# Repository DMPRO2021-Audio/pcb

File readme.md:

# PCB for synth project thingy

## [Bill of materials (google sheets)](https://docs.google.com/spreadsheets/d/1mw8S-eOHjplATXsi4Le0auCMZ8W1ZmBKjRO5l_0JOso/edit#gid=0)

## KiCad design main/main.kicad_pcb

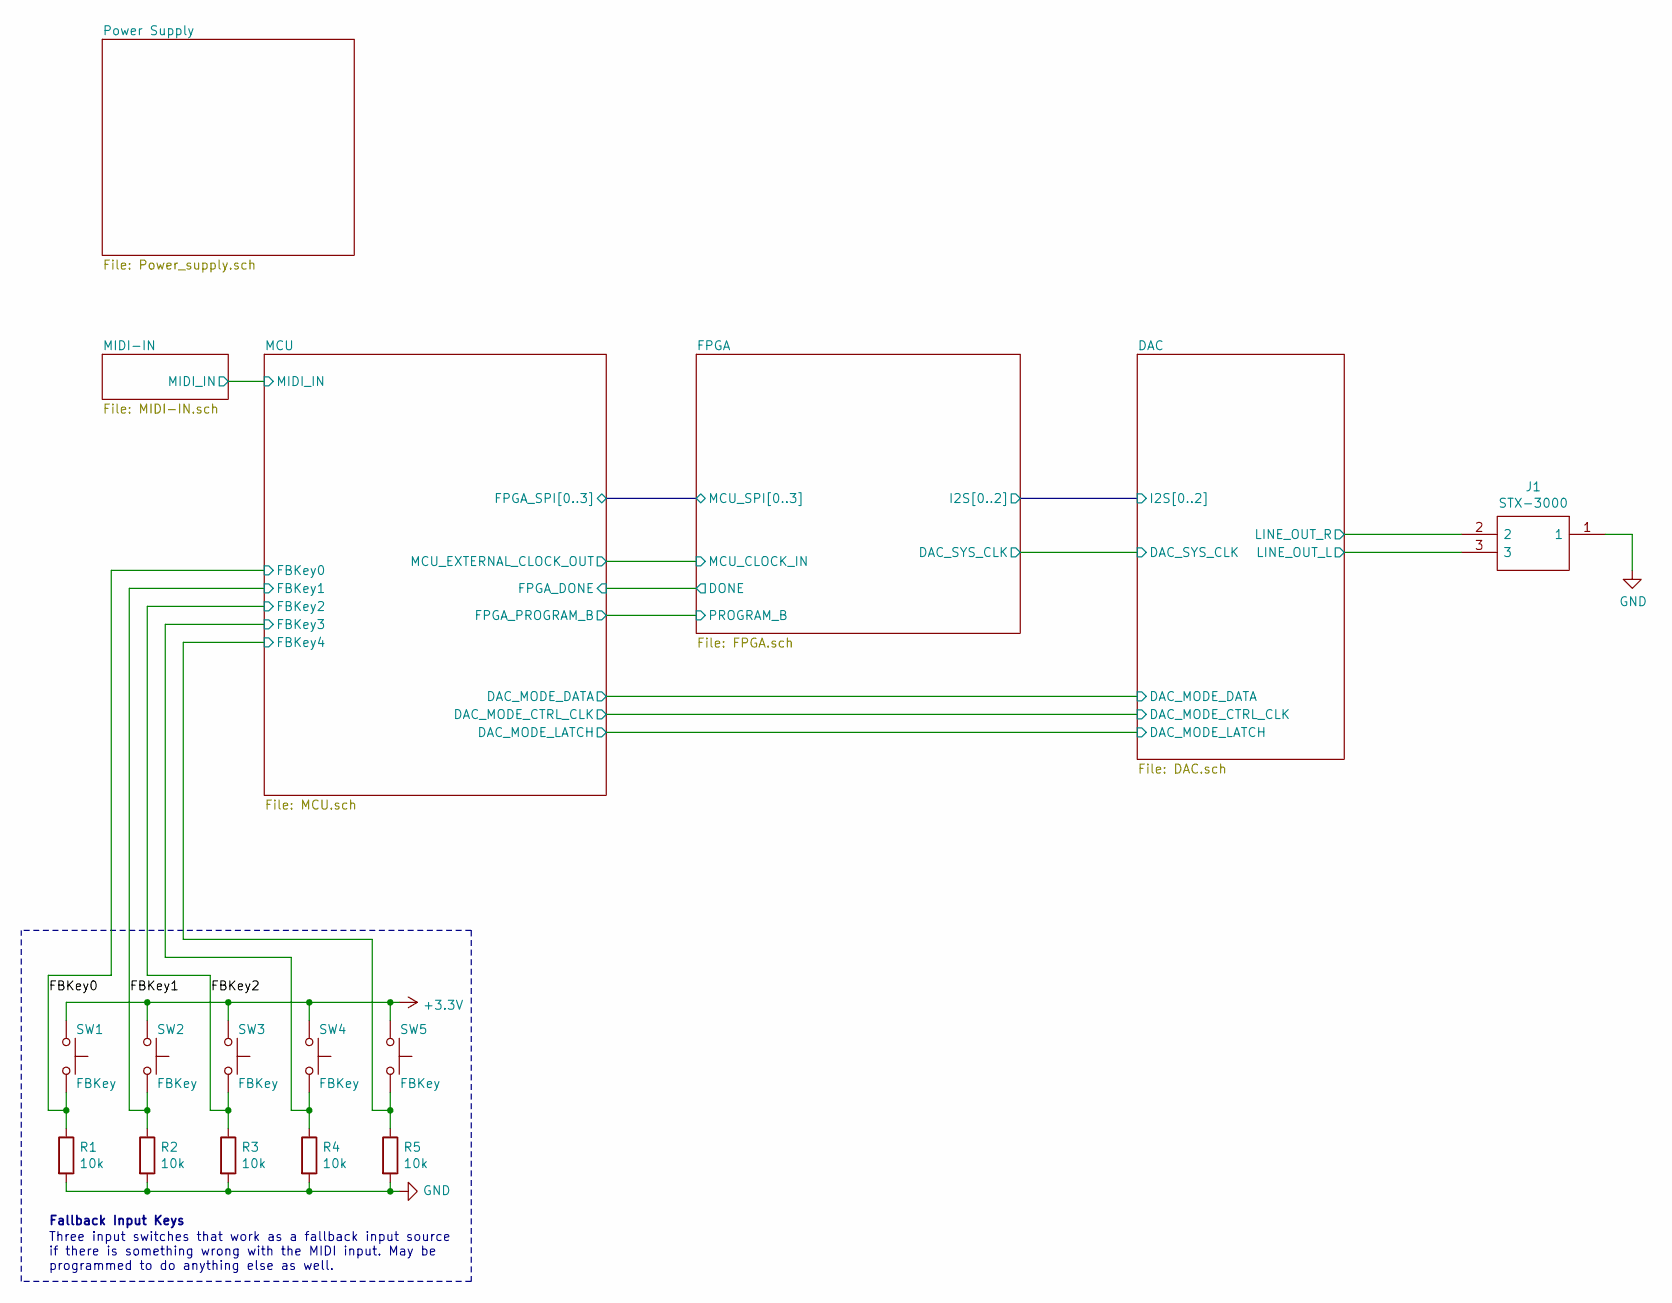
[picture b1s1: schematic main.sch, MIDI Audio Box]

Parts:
J1: STX-3000; STX3000; Manufacturer_Part_Number STX-3000
R1, R2, R3, R4, R5: 10k; R_0805_2012Metric_Pad1.20x1.40mm_HandSolder
SW1, SW2, SW3, SW4, SW5: FBKey; SW_Push_1P1T_NO_6x6mm_H9.5mm; Manufacturer_Part_Number PTS645SM43SMTR92 LFS

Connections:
+3V3: SW1.1, SW2.1, SW3.1, SW4.1, SW5.1; also elsewhere on the board
/DAC/LINE_OUT_L: J1.3; also elsewhere on the board
/DAC/LINE_OUT_R: J1.2; also elsewhere on the board
/FBKey0: R1.1, SW1.2; also elsewhere on the board
/FBKey1: R2.1, SW2.2; also elsewhere on the board
/FBKey2: R3.1, SW3.2; also elsewhere on the board
/MCU/FBKey3: R4.1, SW4.2; also elsewhere on the board
/MCU/FBKey4: R5.1, SW5.2; also elsewhere on the board
GND: J1.1, R1.2, R2.2, R3.2, R4.2, R5.2; also elsewhere on the board

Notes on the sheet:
Fallback Input Keys
Three input switches that work as a fallback input source if there is something wrong with the MIDI input. May be programmed to do anything else as well.

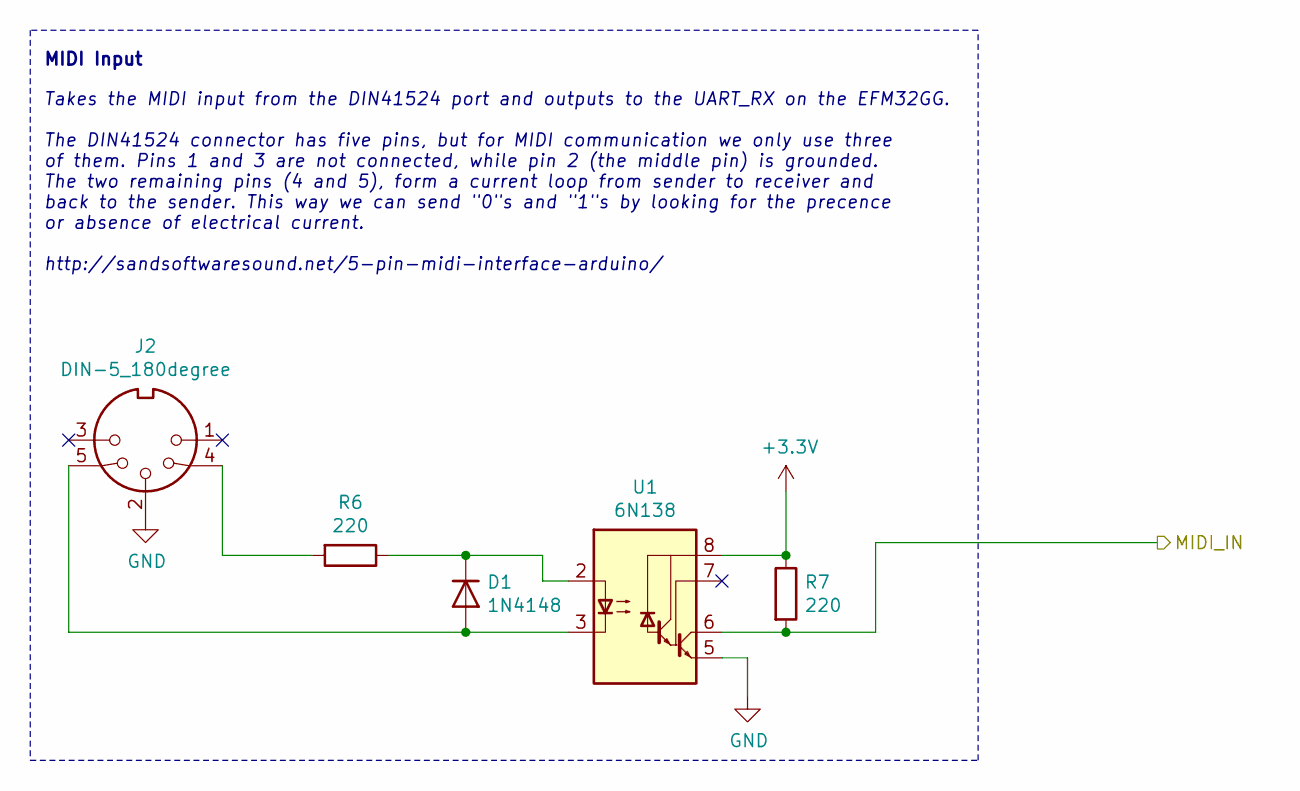
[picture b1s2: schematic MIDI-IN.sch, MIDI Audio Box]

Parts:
D1: 1N4148; D_SOD-123F; Manufacturer_Part_Number 1N4148W RH
J2: DIN-5_180degree; 671-0501; Manufacturer_Part_Number 671-0501
R6, R7: 220; R_0805_2012Metric_Pad1.20x1.40mm_HandSolder
U1: 6N138; SOP254P1030X460-8N; Manufacturer_Part_Number 6N138SMT/R

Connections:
+3V3: R7.1, U1.8 (VCC); also elsewhere on the board
/MCU/MIDI_IN: R7.2, U1.6 (VO2); also elsewhere on the board
GND: J2.2, U1.5 (GND); also elsewhere on the board
unnamed: D1.1 (K), R6.1, U1.2 (C1)
unnamed: D1.2 (A), J2.5, U1.3 (C2)
unnamed: J2.4, R6.2

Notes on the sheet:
MIDI Input
Takes the MIDI input from the DIN41524 port and outputs to the UART_RX on the EFM32GG. The DIN41524 connector has five pins, but for MIDI communication we only use three of them. Pins 1 and 3 are not connected, while pin 2 (the middle pin) is grounded. The two remaining pins (4 and 5), form a curre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

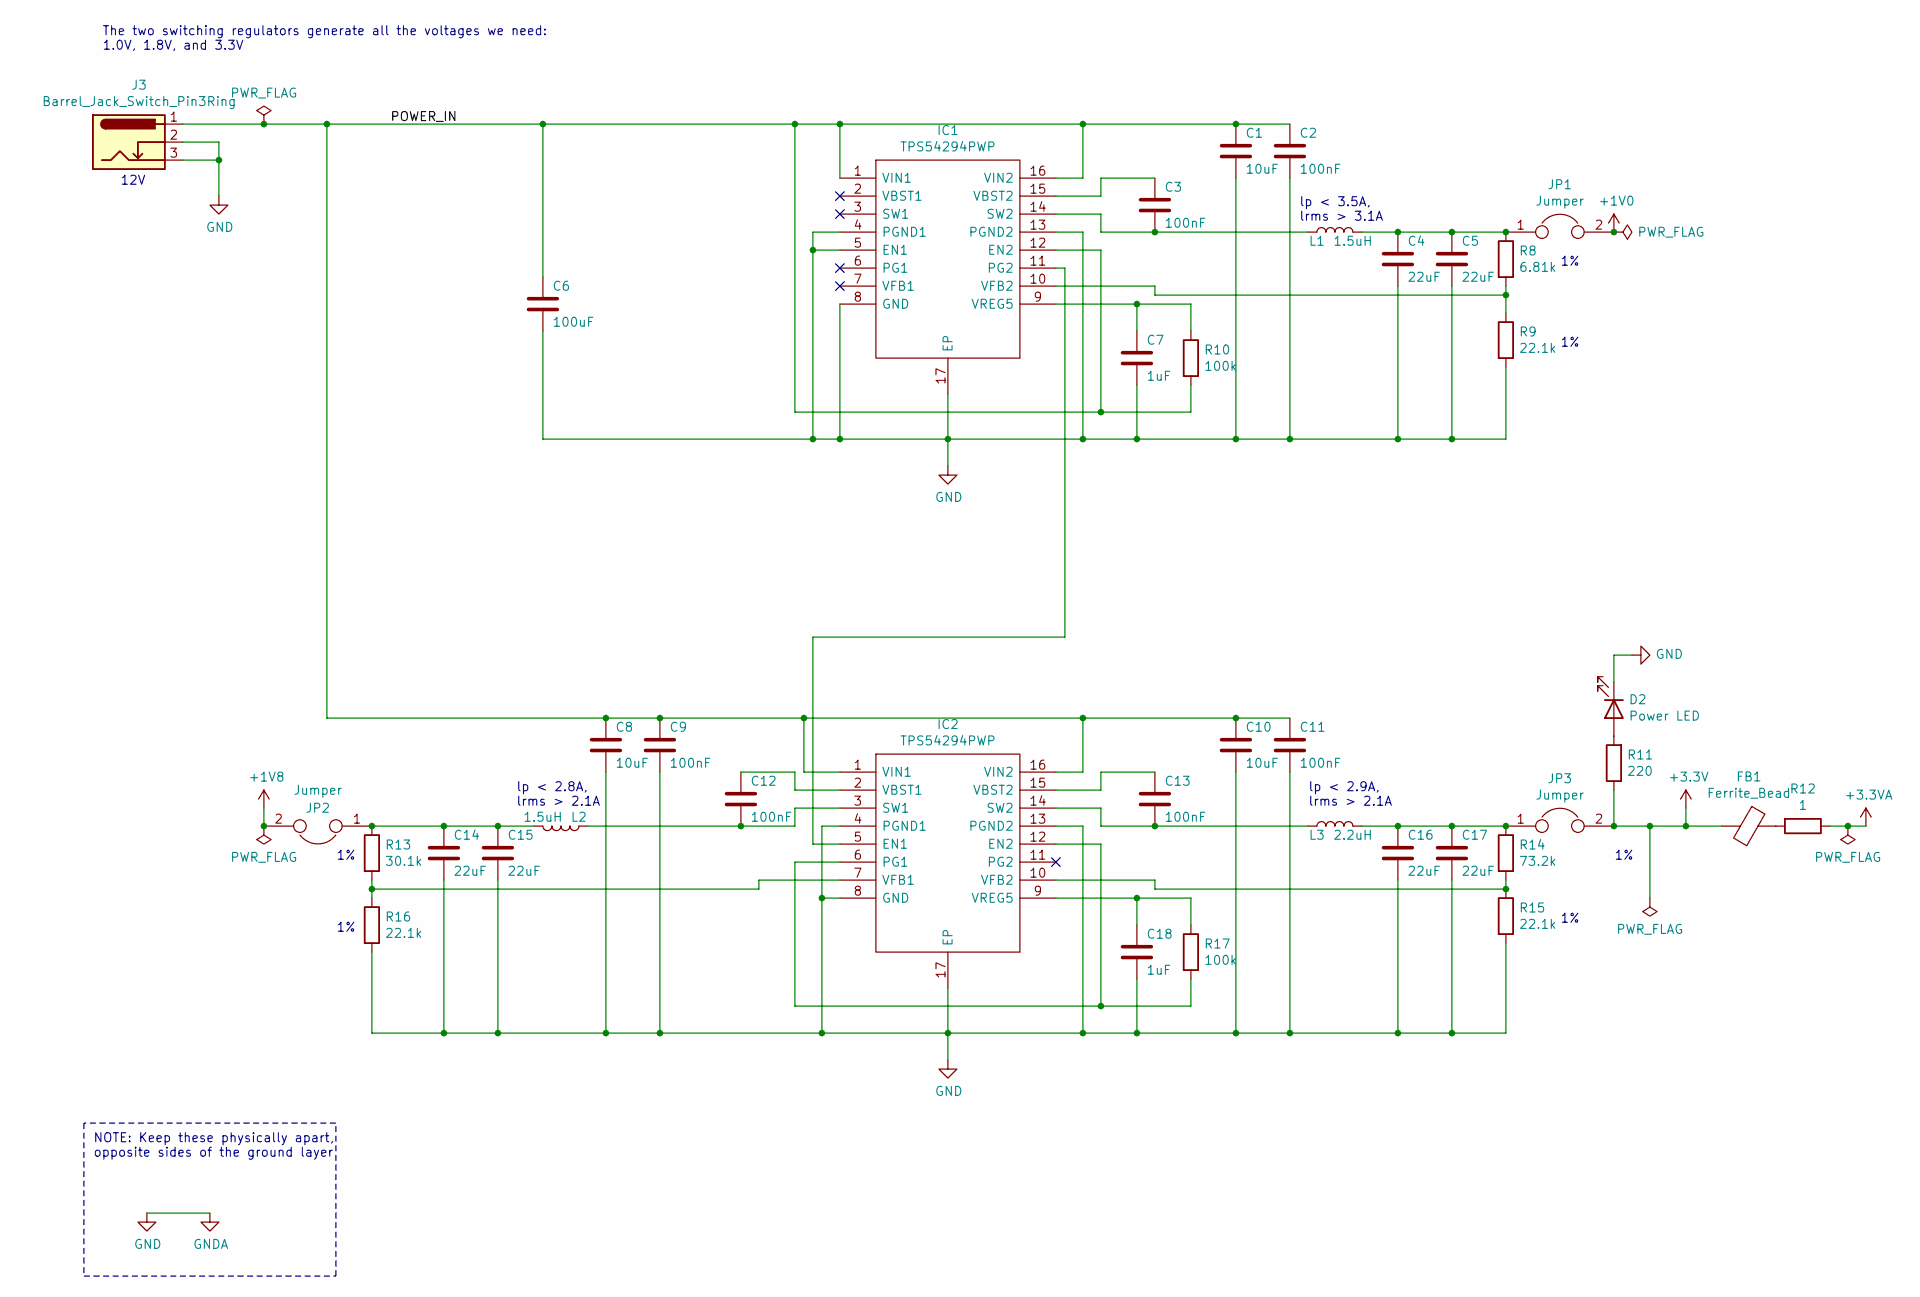
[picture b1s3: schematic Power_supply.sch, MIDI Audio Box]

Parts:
C1, C8, C10: 10uF; C_0805_2012Metric_Pad1.18x1.45mm_HandSolder
C2, C3, C9, C11, C12, C13: 100nF; C_0805_2012Metric_Pad1.18x1.45mm_HandSolder
C4, C5, C14, C15, C16, C17: 22uF; C_0805_2012Metric_Pad1.18x1.45mm_HandSolder
C6: 100uF; C_1210_3225Metric_Pad1.33x2.70mm_HandSolder
C7, C18: 1uF; C_0805_2012Metric_Pad1.18x1.45mm_HandSolder
D2: Power LED; LED_0805_2012Metric_Pad1.15x1.40mm_HandSolder; Manufacturer_Part_Number 150080RS75000
FB1: Ferrite_Bead; R_0805_2012Metric_Pad1.20x1.40mm_HandSolder; Manufacturer_Part_Number BMB2A0060LN2
IC1, IC2: TPS54294PWP; Manufacturer_Part_Number TPS54294PWP; Mouser Part Number 595-TPS54294PWP
J3: Barrel_Jack_Switch_Pin3Ring; BarrelJack_CUI_PJ-102AH_Horizontal; Manufacturer_Part_Number PJ-002A
JP1, JP2, JP3: Jumper; PinHeader_2x01_P2.54mm_Vertical
L1, L2: 1.5uH; L_1806_4516Metric_Pad1.57x1.80mm_HandSolder; Manufacturer_Part_Number 1286AS-H-2R2M=P2
L3: 2.2uH; L_1806_4516Metric_Pad1.57x1.80mm_HandSolder; Manufacturer_Part_Number DFE201610E-1R5M=P2
R8: 6.81k; R_0805_2012Metric_Pad1.20x1.40mm_HandSolder
R9, R15, R16: 22.1k; R_0805_2012Metric_Pad1.20x1.40mm_HandSolder
R10, R17: 100k; R_0805_2012Metric_Pad1.20x1.40mm_HandSolder
R11: 220; R_0805_2012Metric_Pad1.20x1.40mm_HandSolder
R12: 1; R_0805_2012Metric_Pad1.20x1.40mm_HandSolder
R13: 30.1k; R_0805_2012Metric_Pad1.20x1.40mm_HandSolder
R14: 73.2k; R_0805_2012Metric_Pad1.20x1.40mm_HandSolder

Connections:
+1V0: JP1.2; also elsewhere on the board
+1V8: JP2.2; also elsewhere on the board
+3.3VA: R12.1; also elsewhere on the board
+3V3: FB1.2, JP3.2, R11.1; also elsewhere on the board
/Power Supply/POWER_IN: C1.1, C2.1, C6.1, C8.1, C9.1, C10.1, C11.1, IC1.1 (VIN1), IC1.12 (EN2), IC1.16 (VIN2), IC2.1 (VIN1), IC2.16 (VIN2), J3.1, R10.2
GND: C1.2, C2.2, C4.2, C5.2, C6.2, C7.2, C8.2, C9.2, C10.2, C11.2, C14.2, C15.2, C16.2, C17.2, C18.2, D2.1 (K), IC1.4 (PGND1), IC1.5 (EN1), IC1.8 (GND), IC1.13 (PGND2), IC1.17 (EP), IC2.4 (PGND1), IC2.8 (GND), IC2.13 (PGND2), IC2.17 (EP), J3.2, J3.3, R9.2, R15.2, R16.2; also elsewhere on the board
unnamed: C3.1, IC1.15 (VBST2)
unnamed: C3.2, IC1.14 (SW2), L1.1
unnamed: C4.1, C5.1, JP1.1, L1.2, R8.1
unnamed: C7.1, IC1.9 (VREG5), R10.1
unnamed: C12.1, IC2.2 (VBST1)
unnamed: C12.2, IC2.3 (SW1), L2.1
unnamed: C13.1, IC2.15 (VBST2)
unnamed: C13.2, IC2.14 (SW2), L3.1
unnamed: C14.1, C15.1, JP2.1, L2.2, R13.1
unnamed: C16.1, C17.1, JP3.1, L3.2, R14.1
unnamed: C18.1, IC2.9 (VREG5), R17.1
unnamed: D2.2 (A), R11.2
unnamed: FB1.1, R12.2
unnamed: IC1.10 (VFB2), R8.2, R9.1
unnamed: IC1.11 (PG2), IC2.5 (EN1)
unnamed: IC2.7 (VFB1), R13.2, R16.1
unnamed: IC2.10 (VFB2), R14.2, R15.1
unnamed: IC2.6 (PG1), IC2.12 (EN2), R17.2

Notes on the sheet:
lp < 2.8A, lrms > 2.1A
lp < 2.9A, lrms > 2.1A
12V
lp < 3.5A, lrms > 3.1A
The two switching regulators generate all the voltages we need: 1.0V, 1.8V, and 3.3V
NOTE: Keep these physically apart, opposite sides of the ground layer

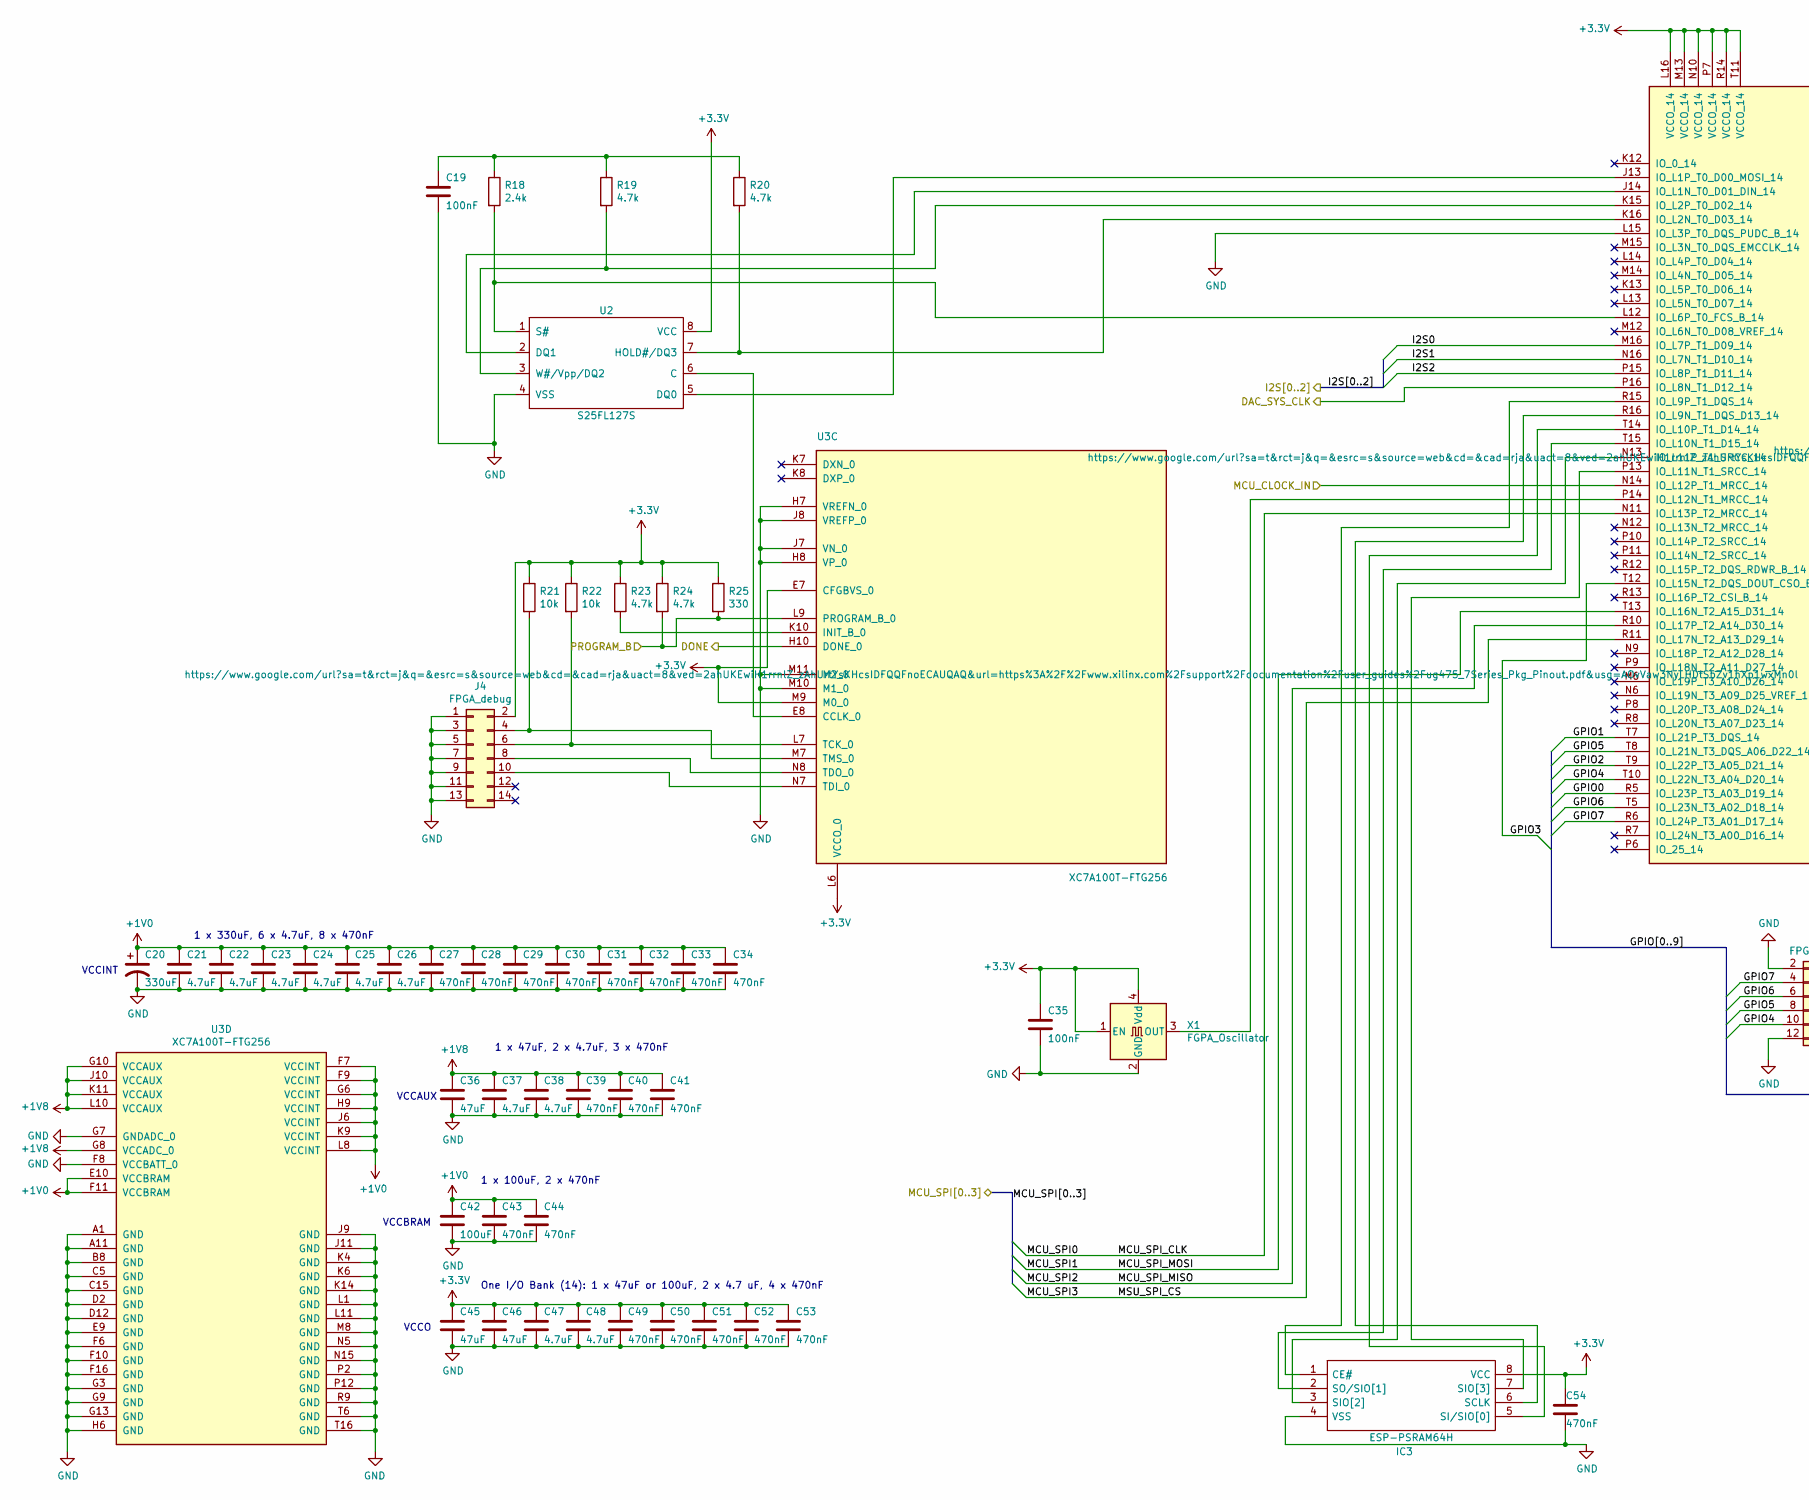
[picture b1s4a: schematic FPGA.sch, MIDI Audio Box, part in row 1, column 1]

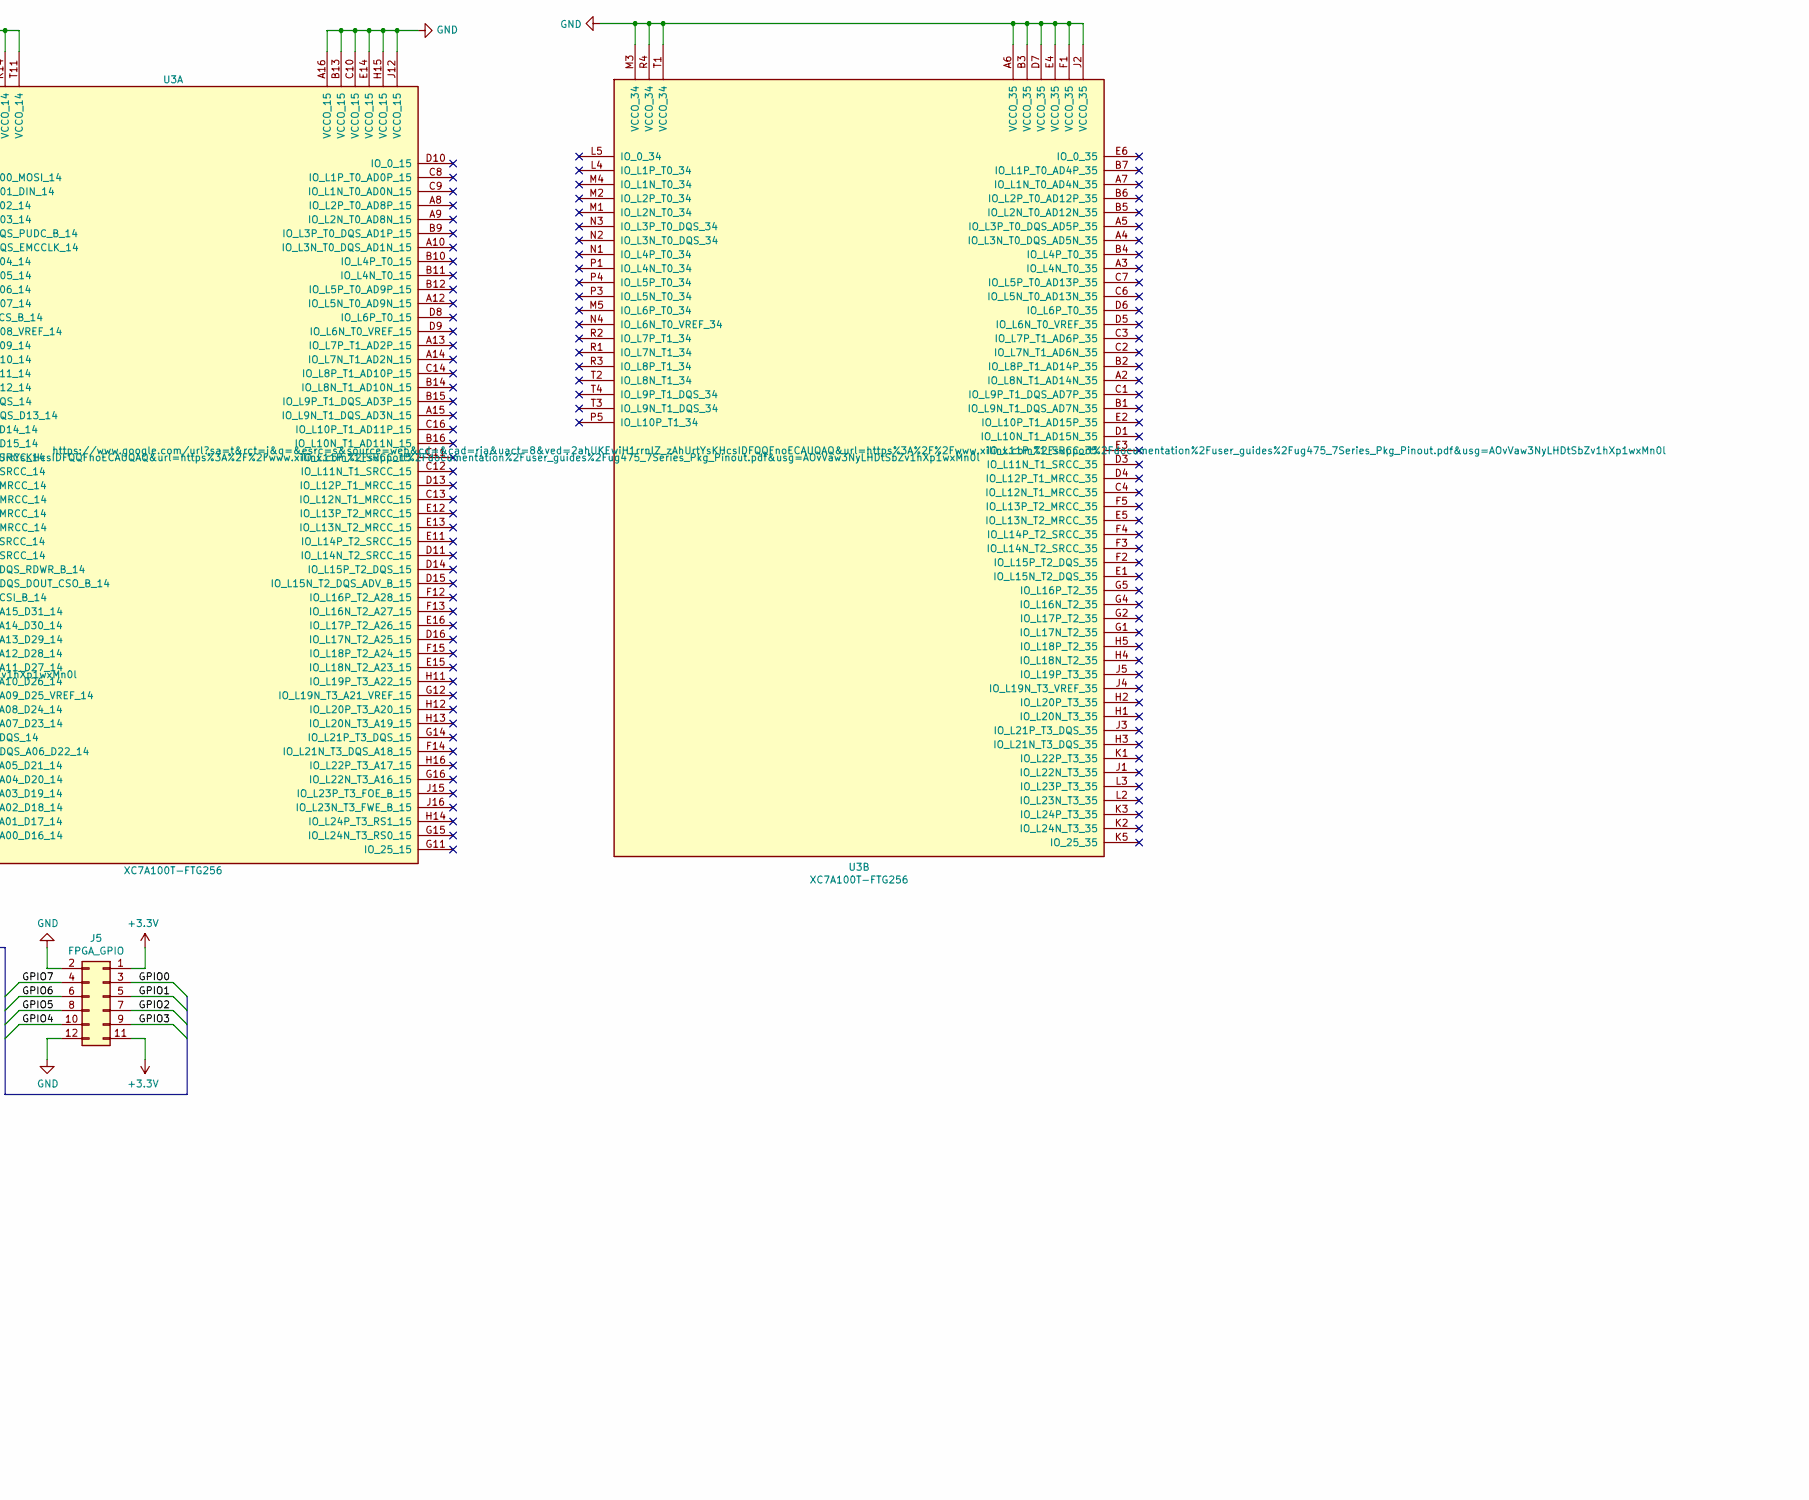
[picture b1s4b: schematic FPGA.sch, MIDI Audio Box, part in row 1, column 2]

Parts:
C19, C35: 100nF; C_0805_2012Metric_Pad1.18x1.45mm_HandSolder
C20: 330uF; CP_EIA-7343-43_Kemet-X_Pad2.25x2.55mm_HandSolder
C21, C22, C23, C24, C25, C26, C37, C38, C47, C48: 4.7uF; C_0805_2012Metric_Pad1.18x1.45mm_HandSolder
C27, C28, C29, C30, C31, C32, C33, C34, C39, C40, C41, C43, C44, C49, C50, C51, C52, C53, C54: 470nF; C_0603_1608Metric_Pad1.08x0.95mm_HandSolder
C36, C45, C46: 47uF; C_1210_3225Metric_Pad1.33x2.70mm_HandSolder
C42: 100uF; C_1210_3225Metric_Pad1.33x2.70mm_HandSolder
IC3: ESP-PSRAM64H; SOIC127P600X175-8N; Manufacturer_Part_Number 4677
J4: FPGA_debug; PinHeader_2x07_P2.00mm_Vertical
J5: FPGA_GPIO; PinHeader_2x06_P2.54mm_Vertical; Manufacturer_Part_Number 2213S-50G
R18: 2.4k; R_0805_2012Metric_Pad1.20x1.40mm_HandSolder
R19, R20, R23, R24: 4.7k; R_0805_2012Metric_Pad1.20x1.40mm_HandSolder
R21, R22: 10k; R_0805_2012Metric_Pad1.20x1.40mm_HandSolder
R25: 330; R_0805_2012Metric_Pad1.20x1.40mm_HandSolder
U2: S25FL127S; SOIC-8_5.275x5.275mm_P1.27mm; Manufacturer_Part_Number S25FL127SABMFV101
U3: XC7A100T-FTG256; Xilinx_FTG256; Manufacturer_Part_Number XC7A100T-FTG256
X1: FGPA_Oscillator; Oscillator_SMD_SeikoEpson_SG210-4Pin_2.5x2.0mm_HandSoldering

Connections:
+1V0: C20.1, C21.1, C22.1, C23.1, C24.1, C25.1, C26.1, C27.1, C28.1, C29.1, C30.1, C31.1, C32.1, C33.1, C34.1, C42.1, C43.1, C44.1, U3.E10 (VCCBRAM), U3.F7 (VCCINT), U3.F9 (VCCINT), U3.F11 (VCCBRAM), U3.G6 (VCCINT), U3.H9 (VCCINT), U3.J6 (VCCINT), U3.K9 (VCCINT), U3.L8 (VCCINT); also elsewhere on the board
+1V8: C36.1, C37.1, C38.1, C39.1, C40.1, C41.1, U3.G8 (VCCADC_0), U3.G10 (VCCAUX), U3.J10 (VCCAUX), U3.K11 (VCCAUX), U3.L10 (VCCAUX); also elsewhere on the board
+3V3: C35.1, C45.1, C46.1, C47.1, C48.1, C49.1, C50.1, C51.1, C52.1, C53.1, C54.1, IC3.8 (VCC), J4.2, J5.1, J5.11, R21.1, R22.1, R23.1, R24.1, R25.1, U2.8 (VCC), U3.E7 (CFGBVS_0), U3.L6 (VCCO_0), U3.L16 (VCCO_14), U3.M9 (M0_0), U3.M13 (VCCO_14), U3.N10 (VCCO_14), U3.P7 (VCCO_14), U3.R14 (VCCO_14), U3.T11 (VCCO_14), X1.1 (EN), X1.4 (Vdd); also elsewhere on the board
/DAC/DAC_SYS_CLK: U3.P16 (IO_L8N_T1_D12_14); also elsewhere on the board
/DAC/I2S0: U3.M16 (IO_L7P_T1_D09_14); also elsewhere on the board
/DAC/I2S1: U3.N16 (IO_L7N_T1_D10_14); also elsewhere on the board
/DAC/I2S2: U3.P15 (IO_L8P_T1_D11_14); also elsewhere on the board
/FPGA/DONE: U3.H10 (DONE_0); also elsewhere on the board
/FPGA/GPIO0: J5.3, U3.R5 (IO_L23P_T3_A03_D19_14)
/FPGA/GPIO1: J5.5, U3.T7 (IO_L21P_T3_DQS_14)
/FPGA/GPIO2: J5.7, U3.T9 (IO_L22P_T3_A05_D21_14)
/FPGA/GPIO3: J5.9, U3.T12 (IO_L15N_T2_DQS_DOUT_CSO_B_14)
/FPGA/GPIO4: J5.10, U3.T10 (IO_L22N_T3_A04_D20_14)
/FPGA/GPIO5: J5.8, U3.T8 (IO_L21N_T3_DQS_A06_D22_14)
/FPGA/GPIO6: J5.6, U3.T5 (IO_L23N_T3_A02_D18_14)
/FPGA/GPIO7: J5.4, U3.R6 (IO_L24P_T3_A01_D17_14)
/FPGA/MCU_CLOCK_IN: U3.N14 (IO_L12P_T1_MRCC_14); also elsewhere on the board
/MCU/FPGA_PROGRAM_B: R24.2, R25.2, U3.L9 (PROGRAM_B_0); also elsewhere on the board
/MCU/FPGA_SPI0: U3.N11 (IO_L13P_T2_MRCC_14); also elsewhere on the board
/MCU/FPGA_SPI1: U3.T13 (IO_L16N_T2_A15_D31_14); also elsewhere on the board
/MCU/FPGA_SPI2: U3.R10 (IO_L17P_T2_A14_D30_14); also elsewhere on the board
/MCU/FPGA_SPI3: U3.R11 (IO_L17N_T2_A13_D29_14); also elsewhere on the board
GND: C19.2, C20.2, C21.2, C22.2, C23.2, C24.2, C25.2, C26.2, C27.2, C28.2, C29.2, C30.2, C31.2, C32.2, C33.2, C34.2, C35.2, C36.2, C37.2, C38.2, C39.2, C40.2, C41.2, C42.2, C43.2, C44.2, C45.2, C46.2, C47.2, C48.2, C49.2, C50.2, C51.2, C52.2, C53.2, C54.2, IC3.4 (VSS), J4.1, J4.3, J4.5, J4.7, J4.9, J4.11, J4.13, J5.2, J5.12, U2.4 (VSS), U3.A1 (GND), U3.A6 (VCCO_35), U3.A11 (GND), U3.A16 (VCCO_15), U3.B3 (VCCO_35), U3.B8 (GND), U3.B13 (VCCO_15), U3.C5 (GND), U3.C10 (VCCO_15), U3.C15 (GND), U3.D2 (GND), U3.D7 (VCCO_35), U3.D12 (GND), U3.E4 (VCCO_35), U3.E9 (GND), U3.E14 (VCCO_15), U3.F1 (VCCO_35), U3.F6 (GND), U3.F8 (VCCBATT_0), U3.F10 (GND), U3.F16 (GND), U3.G3 (GND), U3.G7 (GNDADC_0), U3.G9 (GND), U3.G13 (GND), U3.H6 (GND), U3.H7 (VREFN_0), U3.H8 (VP_0), U3.H15 (VCCO_15), U3.J2 (VCCO_35), U3.J7 (VN_0), U3.J8 (VREFP_0), U3.J9 (GND), U3.J11 (GND), U3.J12 (VCCO_15), U3.K4 (GND), U3.K6 (GND), U3.K14 (GND), U3.L1 (GND), U3.L11 (GND), U3.L15 (IO_L3P_T0_DQS_PUDC_B_14), U3.M3 (VCCO_34), U3.M8 (GND), U3.M10 (M1_0), U3.M11 (M2_0), U3.N5 (GND), U3.N15 (GND), U3.P2 (GND), U3.P12 (GND), U3.R4 (VCCO_34), U3.R9 (GND), U3.T1 (VCCO_34), U3.T6 (GND), U3.T16 (GND), X1.2 (GND); also elsewhere on the board
unnamed: C19.1, R18.1, R19.1, R20.1
unnamed: IC3.1 (CE#), U3.R15 (IO_L9P_T1_DQS_14)
unnamed: IC3.2 (SO/SIO[1]), U3.T15 (IO_L10N_T1_D15_14)
unnamed: IC3.3 (SIO[2]), U3.N13 (IO_L11P_T1_SRCC_14)
unnamed: IC3.5 (SI/SIO[0]), U3.T14 (IO_L10P_T1_D14_14)
unnamed: IC3.6 (SCLK), U3.R16 (IO_L9N_T1_DQS_D13_14)
unnamed: IC3.7 (SIO[3]), U3.P13 (IO_L11N_T1_SRCC_14)
unnamed: J4.4, R21.2, U3.M7 (TMS_0)
unnamed: J4.6, R22.2, U3.L7 (TCK_0)
unnamed: J4.8, U3.N8 (TDO_0)
unnamed: J4.10, U3.N7 (TDI_0)
unnamed: R18.2, U2.1 (S#), U3.L12 (IO_L6P_T0_FCS_B_14)
unnamed: R19.2, U2.3 (W#/Vpp/DQ2), U3.K15 (IO_L2P_T0_D02_14)
unnamed: R20.2, U2.7 (HOLD#/DQ3), U3.K16 (IO_L2N_T0_D03_14)
unnamed: R23.2, U3.K10 (INIT_B_0)
unnamed: U2.2 (DQ1), U3.J14 (IO_L1N_T0_D01_DIN_14)
unnamed: U2.5 (DQ0), U3.J13 (IO_L1P_T0_D00_MOSI_14)
unnamed: U2.6 (C), U3.E8 (CCLK_0)
unnamed: U3.P14 (IO_L12N_T1_MRCC_14), X1.3 (OUT)

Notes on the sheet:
VCCINT
VCCBRAM
VCCAUX
VCCO
1 x 330uF, 6 x 4.7uF, 8 x 470nF
1 x 47uF, 2 x 4.7uF, 3 x 470nF
1 x 100uF, 2 x 470nF
One I/O Bank (14): 1 x 47uF or 100uF, 2 x 4.7 uF, 4 x 470nF

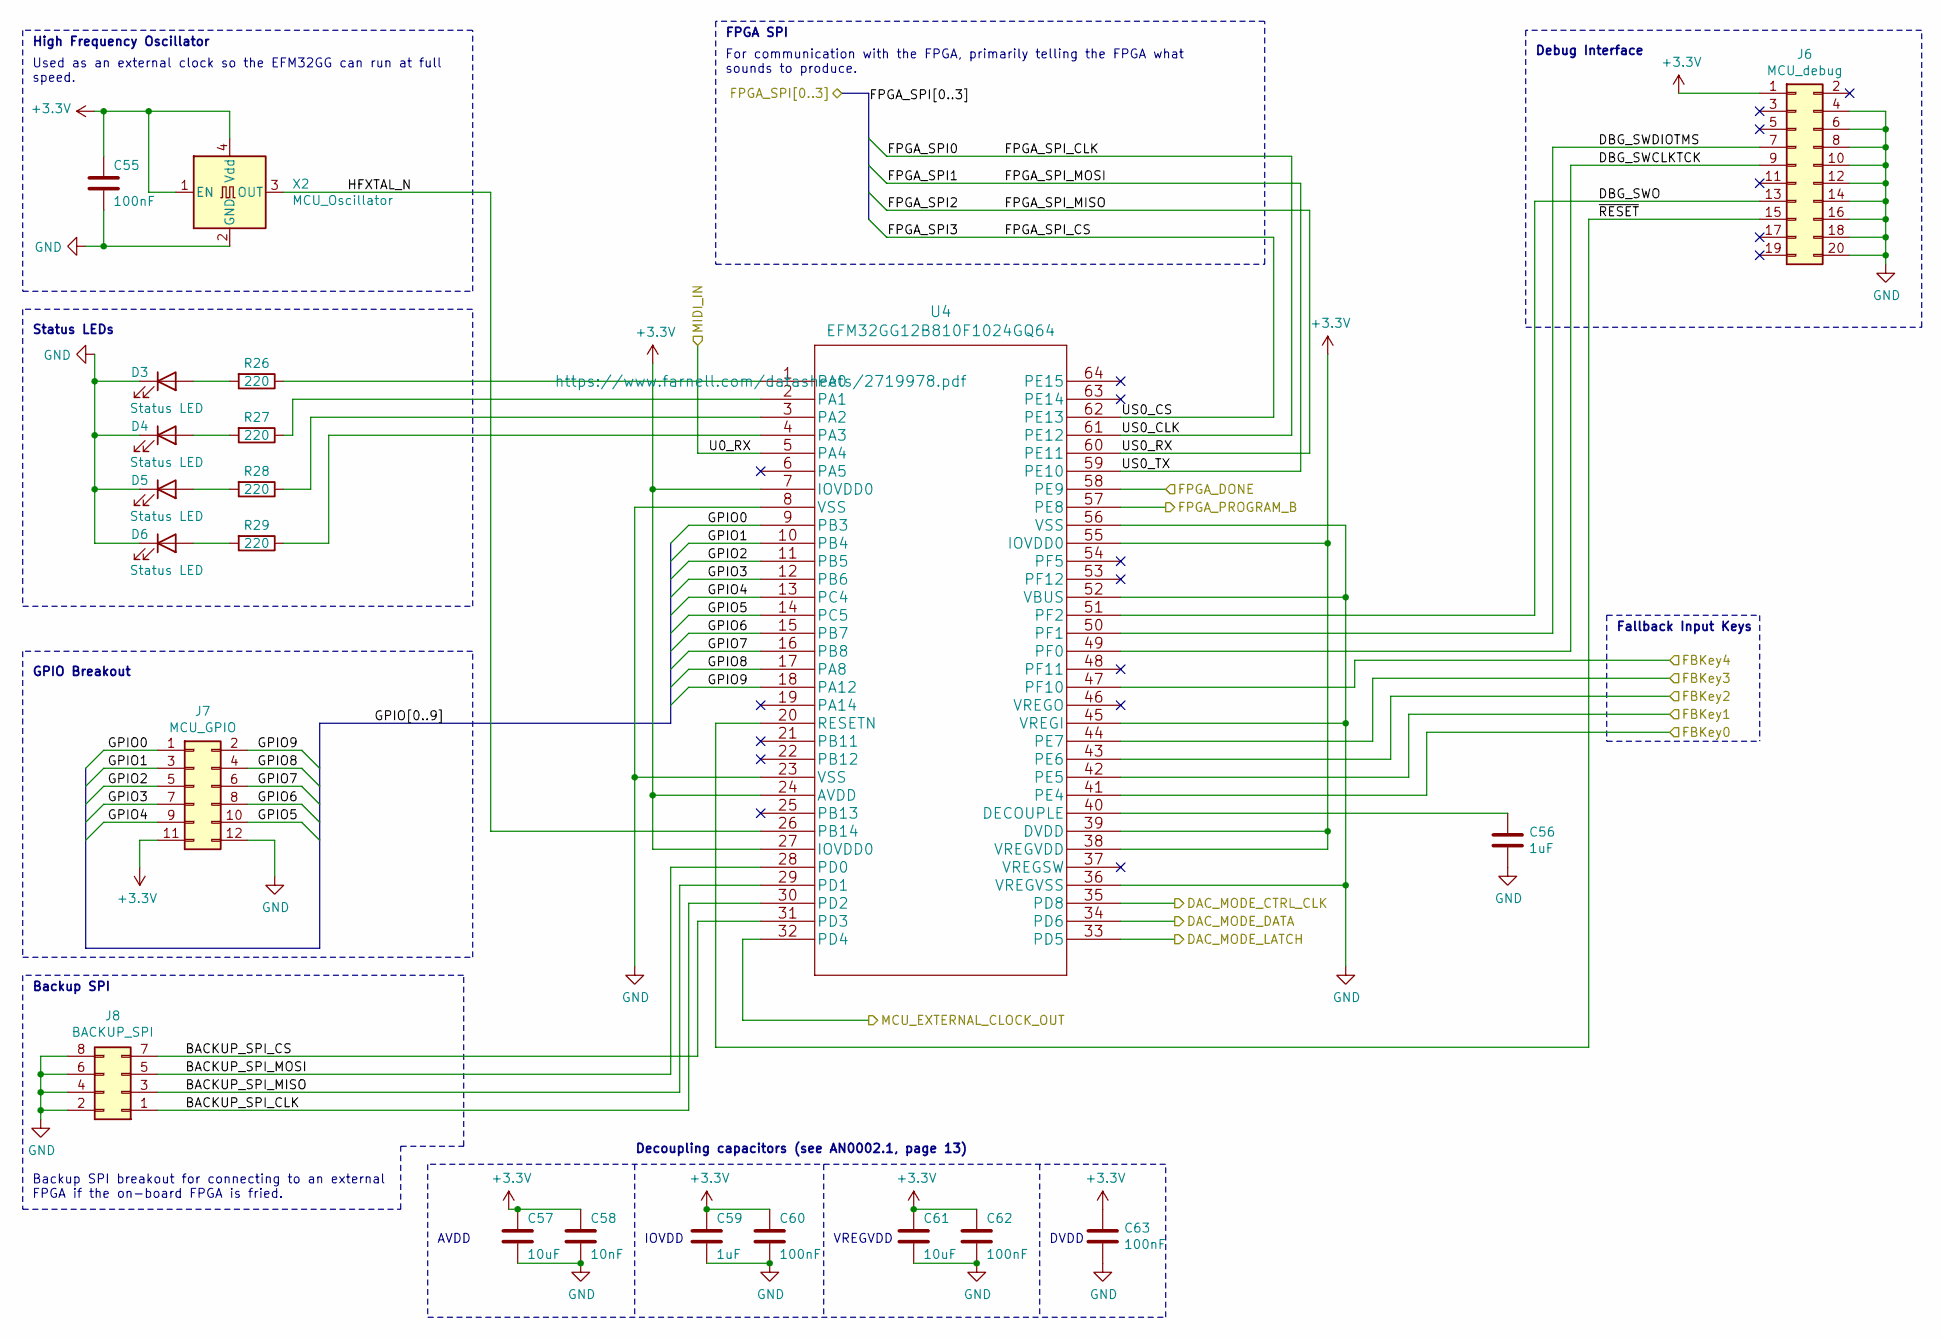
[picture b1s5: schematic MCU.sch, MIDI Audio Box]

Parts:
C55, C60, C62, C63: 100nF; C_0805_2012Metric_Pad1.18x1.45mm_HandSolder
C56, C59: 1uF; C_0805_2012Metric_Pad1.18x1.45mm_HandSolder
C57, C61: 10uF; C_0805_2012Metric_Pad1.18x1.45mm_HandSolder
C58: 10nF; C_0805_2012Metric_Pad1.18x1.45mm_HandSolder
D3, D4, D5, D6: Status LED; LED_0805_2012Metric_Pad1.15x1.40mm_HandSolder; Manufacturer_Part_Number 150080RS75000
J6: MCU_debug; PinHeader_2x10_P1.27mm_Vertical
J7: MCU_GPIO; PinHeader_2x06_P2.54mm_Vertical
J8: BACKUP_SPI; PinHeader_2x04_P2.54mm_Vertical
R26, R27, R28, R29: 220; R_0805_2012Metric_Pad1.20x1.40mm_HandSolder
U4: EFM32GG12B810F1024GQ64; Manufacturer_Part_Number EFM32GG12B810F1024GQ64-A
X2: MCU_Oscillator; Oscillator_SMD_SeikoEpson_SG210-4Pin_2.5x2.0mm_HandSoldering

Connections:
+3V3: C55.1, C57.1, C58.1, C59.1, C60.1, C61.1, C62.1, C63.1, J6.1, J7.11, U4.7 (IOVDD0), U4.24 (AVDD), U4.27 (IOVDD0), U4.38 (VREGVDD), U4.39 (DVDD), U4.55 (IOVDD0), X2.1 (EN), X2.4 (Vdd); also elsewhere on the board
/DAC/DAC_MODE_CTRL_CLK: U4.35 (PD8); also elsewhere on the board
/DAC/DAC_MODE_DATA: U4.34 (PD6); also elsewhere on the board
/DAC/DAC_MODE_LATCH: U4.33 (PD5); also elsewhere on the board
/FBKey0: U4.41 (PE4); also elsewhere on the board
/FBKey1: U4.42 (PE5); also elsewhere on the board
/FBKey2: U4.43 (PE6); also elsewhere on the board
/FPGA/DONE: U4.58 (PE9); also elsewhere on the board
/FPGA/MCU_CLOCK_IN: U4.32 (PD4); also elsewhere on the board
/MCU/BACKUP_SPI_CLK: J8.1, U4.30 (PD2)
/MCU/BACKUP_SPI_CS: J8.7, U4.31 (PD3)
/MCU/BACKUP_SPI_MISO: J8.3, U4.29 (PD1)
/MCU/BACKUP_SPI_MOSI: J8.5, U4.28 (PD0)
/MCU/DBG_SWCLKTCK: J6.9, U4.49 (PF0)
/MCU/DBG_SWDIOTMS: J6.7, U4.50 (PF1)
/MCU/DBG_SWO: J6.13, U4.51 (PF2)
/MCU/FBKey3: U4.44 (PE7); also elsewhere on the board
/MCU/FBKey4: U4.47 (PF10); also elsewhere on the board
/MCU/FPGA_PROGRAM_B: U4.57 (PE8); also elsewhere on the board
/MCU/FPGA_SPI0: U4.61 (PE12); also elsewhere on the board
/MCU/FPGA_SPI1: U4.59 (PE10); also elsewhere on the board
/MCU/FPGA_SPI2: U4.60 (PE11); also elsewhere on the board
/MCU/FPGA_SPI3: U4.62 (PE13); also elsewhere on the board
/MCU/GPIO0: J7.1, U4.9 (PB3)
/MCU/GPIO1: J7.3, U4.10 (PB4)
/MCU/GPIO2: J7.5, U4.11 (PB5)
/MCU/GPIO3: J7.7, U4.12 (PB6)
/MCU/GPIO4: J7.9, U4.13 (PC4)
/MCU/GPIO5: J7.10, U4.14 (PC5)
/MCU/GPIO6: J7.8, U4.15 (PB7)
/MCU/GPIO7: J7.6, U4.16 (PB8)
/MCU/GPIO8: J7.4, U4.17 (PA8)
/MCU/GPIO9: J7.2, U4.18 (PA12)
/MCU/HFXTAL_N: U4.26 (PB14), X2.3 (OUT)
/MCU/MIDI_IN: U4.5 (PA4); also elsewhere on the board
/MCU/~RESET: J6.15, U4.20 (RESETN)
GND: C55.2, C56.2, C57.2, C58.2, C59.2, C60.2, C61.2, C62.2, C63.2, D3.1 (K), D4.1 (K), D5.1 (K), D6.1 (K), J6.4, J6.6, J6.8, J6.10, J6.12, J6.14, J6.16, J6.18, J6.20, J7.12, J8.2, J8.4, J8.6, J8.8, U4.8 (VSS), U4.23 (VSS), U4.36 (VREGVSS), U4.45 (VREGI), U4.52 (VBUS), U4.56 (VSS), X2.2 (GND); also elsewhere on the board
unnamed: C56.1, U4.40 (DECOUPLE)
unnamed: D3.2 (A), R26.2
unnamed: D4.2 (A), R27.2
unnamed: D5.2 (A), R28.2
unnamed: D6.2 (A), R29.2
unnamed: R26.1, U4.1 (PA0)
unnamed: R27.1, U4.2 (PA1)
unnamed: R28.1, U4.3 (PA2)
unnamed: R29.1, U4.4 (PA3)

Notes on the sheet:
VREGVDD
AVDD
IOVDD
DVDD
Backup SPI breakout for connecting to an external FPGA if the on-board FPGA is fried.
Status LEDs
GPIO Breakout
Debug Interface
Fallback Input Keys
FPGA SPI
For communication with the FPGA, primarily telling the FPGA what sounds to produce.
Backup SPI
Decoupling capacitors (see AN0002.1, page 13)
Used as an external clock so the EFM32GG can run at full speed.
High Frequency Oscillator

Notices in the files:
parts and their libraries:
Copyright 2021 Accelerated Designs. All rights reserved.
